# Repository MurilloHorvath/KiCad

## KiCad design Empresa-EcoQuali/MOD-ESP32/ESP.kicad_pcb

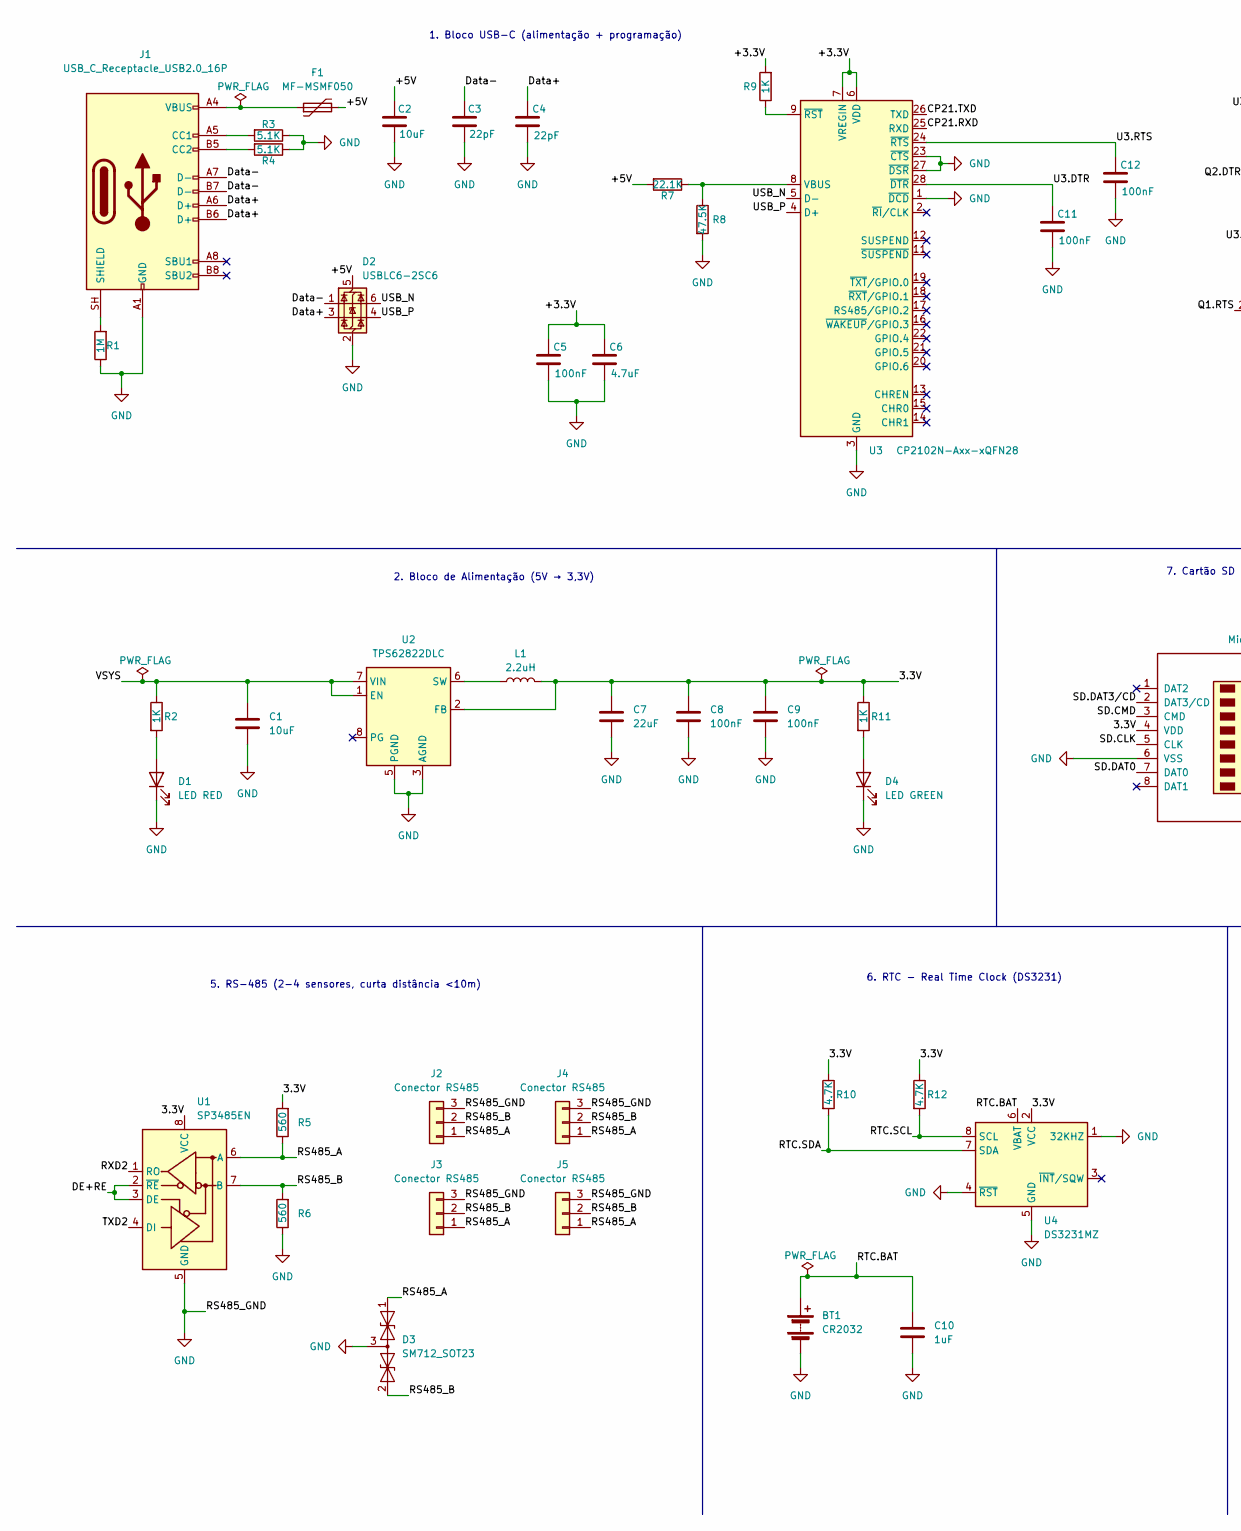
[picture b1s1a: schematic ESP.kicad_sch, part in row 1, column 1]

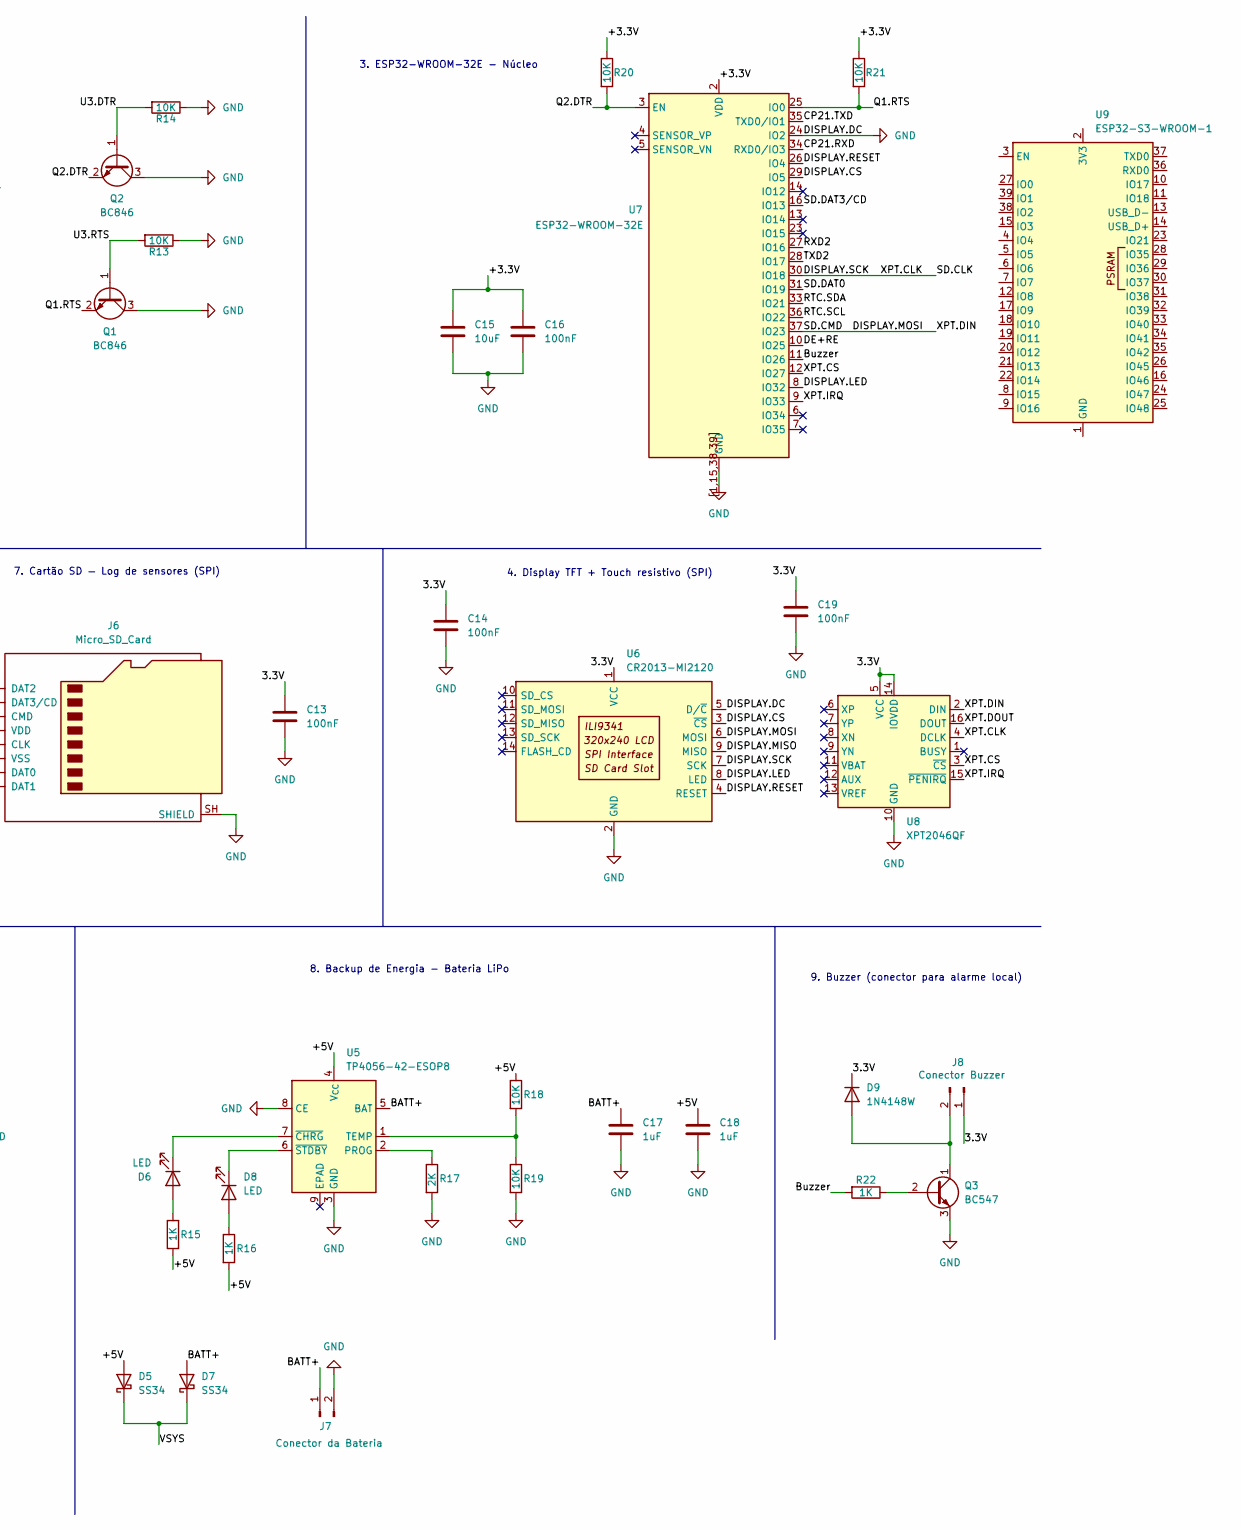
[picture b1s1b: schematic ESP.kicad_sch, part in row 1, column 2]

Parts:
BT1: CR2032; BatteryHolder_Keystone_103_1x20mm
C1, C2, C15: 10uF; C_0805_2012Metric
C3, C4: 22pF; C_0603_1608Metric
C5, C8, C9, C11, C12, C13, C14, C16, C19: 100nF; C_0603_1608Metric
C6: 4.7uF; C_0603_1608Metric
C7: 22uF; C_0805_2012Metric
C10, C17, C18: 1uF; C_0603_1608Metric
D1: LED RED; LED_0603_1608Metric
D2: USBLC6-2SC6; SOT-23-6
D3: SM712_SOT23; SOT-23
D4: LED GREEN; LED_0603_1608Metric
D5, D7: SS34; D_SMA
D6, D8: LED; LED_0603_1608Metric
D9: 1N4148W; D_DO-35_SOD27_P12.70mm_Horizontal
F1: MF-MSMF050; Fuse_1206_3216Metric
J1: USB_C_Receptacle_USB2.0_16P; USB_C_Receptacle_GCT_USB4105-xx-A_16P_TopMnt_Horizontal
J2, J3, J4, J5: Conector RS485; PinHeader_1x03_P2.54mm_Vertical
J6: Micro_SD_Card; microSD_HC_Molex_104031-0811
J7: Conector da Bateria; JST_XH_B2B-XH-A_1x02_P2.50mm_Vertical
J8: Conector Buzzer; JST_XH_B2B-XH-A_1x02_P2.50mm_Vertical
L1: 2.2uH; L_0805_2012Metric
Q1, Q2: BC846; SOT-23
Q3: BC547; TO-92_Inline
R1: 1M; R_0603_1608Metric
R2, R9, R11, R15, R16, R22: 1K; R_0603_1608Metric
R3, R4: 5.1K; R_0603_1608Metric
R5, R6: 560; R_0603_1608Metric
R7: 22.1K; R_0603_1608Metric
R8: 47.5K; R_0603_1608Metric
R10, R12: 4.7K; R_0603_1608Metric
R13, R14, R18, R19, R20, R21: 10K; R_0603_1608Metric
R17: 2K; R_0603_1608Metric
U1: SP3485EN; SOIC-8_3.9x4.9mm_P1.27mm
U2: TPS62822DLC; Texas_VSON-HR-8_1.5x2mm_P0.5mm
U3: CP2102N-Axx-xQFN28; QFN-28-1EP_5x5mm_P0.5mm_EP3.35x3.35mm_ThermalVias
U4: DS3231MZ; SOIC-16_3.9x9.9mm_P1.27mm
U5: TP4056-42-ESOP8; SOIC-8_3.9x4.9mm_P1.27mm
U6: CR2013-MI2120
U7: ESP32-WROOM-32E
U8: XPT2046QF; QFN-16-1EP_4x4mm_P0.65mm_EP2.1x2.1mm
U9: ESP32-S3-WROOM-1

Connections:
/3.3V: C7.1, C8.1, C9.1, C13.1, C14.1, C19.1, D9.1 (K), J6.4 (VDD), J8.1, L1.2, R5.2, R10.1, R11.1, R12.1, U1.8 (VCC), U2.2 (FB), U4.2 (VCC), U6.1 (VCC), U8.5 (VCC), U8.14 (IOVDD)
/+3.3V: C5.1, C6.1, C15.1, C16.1, R9.2, R20.1, R21.1, U3.6 (VDD), U3.7 (VREGIN), U7.2 (VDD)
/+5V: C2.1, C18.1, D2.5 (VBUS), D5.2 (A), F1.2, R7.2, R15.1, R16.2, R18.1, U5.4 (V_{CC})
/BATT+: C17.1, D7.2 (A), J7.1, U5.5 (BAT)
/Buzzer: R22.2, U7.11 (IO26)
/CP21.RXD: U3.25 (RXD), U7.34 (RXD0/IO3)
/CP21.TXD: U3.26 (TXD), U7.35 (TXD0/IO1)
/DE+RE: U1.2 (~RE), U1.3 (DE), U7.10 (IO25)
/DISPLAY.CS: U6.3 (~CS), U7.29 (IO5)
/DISPLAY.LED: U6.8 (LED), U7.8 (IO32)
/DISPLAY.MISO: U6.9 (MISO)
/DISPLAY.MOSI: J6.3 (CMD), U6.6 (MOSI), U7.37 (IO23), U8.2 (DIN)
/DISPLAY.RESET: U6.4 (RESET), U7.26 (IO4)
/DISPLAY.SCK: J6.5 (CLK), U6.7 (SCK), U7.30 (IO18), U8.4 (DCLK)
/Data+: C4.1, D2.3 (I/O2), J1.A6 (D+), J1.B6 (D+)
/Data-: C3.1, D2.1 (I/O1), J1.A7 (D-), J1.B7 (D-)
/Q1.RTS: Q1.2 (E), R21.2, U7.25 (IO0)
/Q2.DTR: Q2.2 (E), R20.2, U7.3 (EN)
/RS485_A: D3.1 (A1), J2.1, J3.1, J4.1, J5.1, R5.1, U1.6 (A)
/RS485_B: D3.2 (A2), J2.2, J3.2, J4.2, J5.2, R6.2, U1.7 (B)
/RTC.BAT: BT1.1 (+), C10.1, U4.6 (VBAT)
/RTC.SCL: R12.2, U4.8 (SCL), U7.36 (IO22)
/RTC.SDA: R10.2, U4.7 (SDA), U7.33 (IO21)
/RXD2: U1.1 (RO), U7.27 (IO16)
/SD.DAT0: J6.7 (DAT0), U7.31 (IO19)
/SD.DAT3/CD: J6.2 (DAT3/CD), U7.16 (IO13)
/TXD2: U1.4 (DI), U7.28 (IO17)
/U3.DTR: C11.1, Q2.1 (B), R14.2, U3.28 (~DTR)
/U3.RTS: C12.1, Q1.1 (B), R13.2, U3.24 (~RTS)
/USB_N: D2.6 (I/O1), U3.5 (D-)
/USB_P: D2.4 (I/O2), U3.4 (D+)
/VSYS: C1.1, D5.1 (K), D7.1 (K), R2.1, U2.1 (EN), U2.7 (VIN)
/XPT.CS: U7.12 (IO27), U8.3 (~CS)
/XPT.DOUT: U8.16 (DOUT)
/XPT.IRQ: U7.9 (IO33), U8.15 (~PENIRQ)
GND: BT1.2 (-), C1.2, C2.2, C3.2, C4.2, C5.2, C6.2, C7.2, C8.2, C9.2, C10.2, C11.2, C12.2, C13.2, C14.2, C15.2, C16.2, C17.2, C18.2, C19.2, D1.1 (K), D2.2 (GND), D3.3 (common), D4.1 (K), J1.A1 (GND), J1.A12 (GND), J1.B1 (GND), J1.B12 (GND), J2.3, J3.3, J4.3, J5.3, J6.6 (VSS), J6.SH (SHIELD), J7.2, Q1.3 (C), Q2.3 (C), Q3.3 (E), R1.1, R3.1, R4.1, R6.1, R8.2, R13.1, R14.1, R17.2, R19.2, U1.5 (GND), U2.3 (AGND), U2.5 (PGND), U3.1 (~DCD), U3.3 (GND), U3.23 (~CTS), U3.27 (~DSR), U3.29 (GND), U4.1 (32KHZ), U4.4 (~RST), U4.5 (GND), U5.3 (GND), U5.8 (CE), U6.2 (GND), U6.5 (D/~C), U7.1 (GND), U7.15 (GND), U7.24 (IO2), U7.38 (GND), U7.39 (GND), U7.[1,15,38,39] (GND), U8.10 (GND)
unnamed: D1.2 (A), R2.2
unnamed: D4.2 (A), R11.2
unnamed: D6.2 (A), R15.2
unnamed: D6.1 (K), U5.7 (~CHRG)
unnamed: D8.2 (A), R16.1
unnamed: D8.1 (K), U5.6 (~STDBY)
unnamed: D9.2 (A), J8.2, Q3.1 (C)
unnamed: F1.1, J1.A4 (VBUS), J1.A9 (VBUS), J1.B4 (VBUS), J1.B9 (VBUS)
unnamed: J1.A5 (CC1), R3.2
unnamed: J1.B5 (CC2), R4.2
unnamed: J1.SH (SHIELD), R1.2
unnamed: Q3.2 (B), R22.1
unnamed: L1.1, U2.6 (SW)
unnamed: R7.1, R8.1, U3.8 (VBUS)
unnamed: R9.1, U3.9 (~RST)
unnamed: R17.1, U5.2 (PROG)
unnamed: R18.2, R19.1, U5.1 (TEMP)
unnamed: U9.1 (GND), U9.40 (GND), U9.41 (GND)

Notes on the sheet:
9. Buzzer (conector para alarme local)
6. RTC - Real Time Clock (DS3231)
3. ESP32-WROOM-32E - Núcleo
5. RS-485 (2-4 sensores, curta distância <10m)
7. Cartão SD — Log de sensores (SPI)
4. Display TFT + Touch resistivo (SPI)
2. Bloco de Alimentação (5V → 3,3V)
8. Backup de Energia - Bateria LiPo
1. Bloco USB-C (alimentação + programação)

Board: 2 copper layers, 72 parts (71 on the bottom side), 51 nets, no tracks yet.

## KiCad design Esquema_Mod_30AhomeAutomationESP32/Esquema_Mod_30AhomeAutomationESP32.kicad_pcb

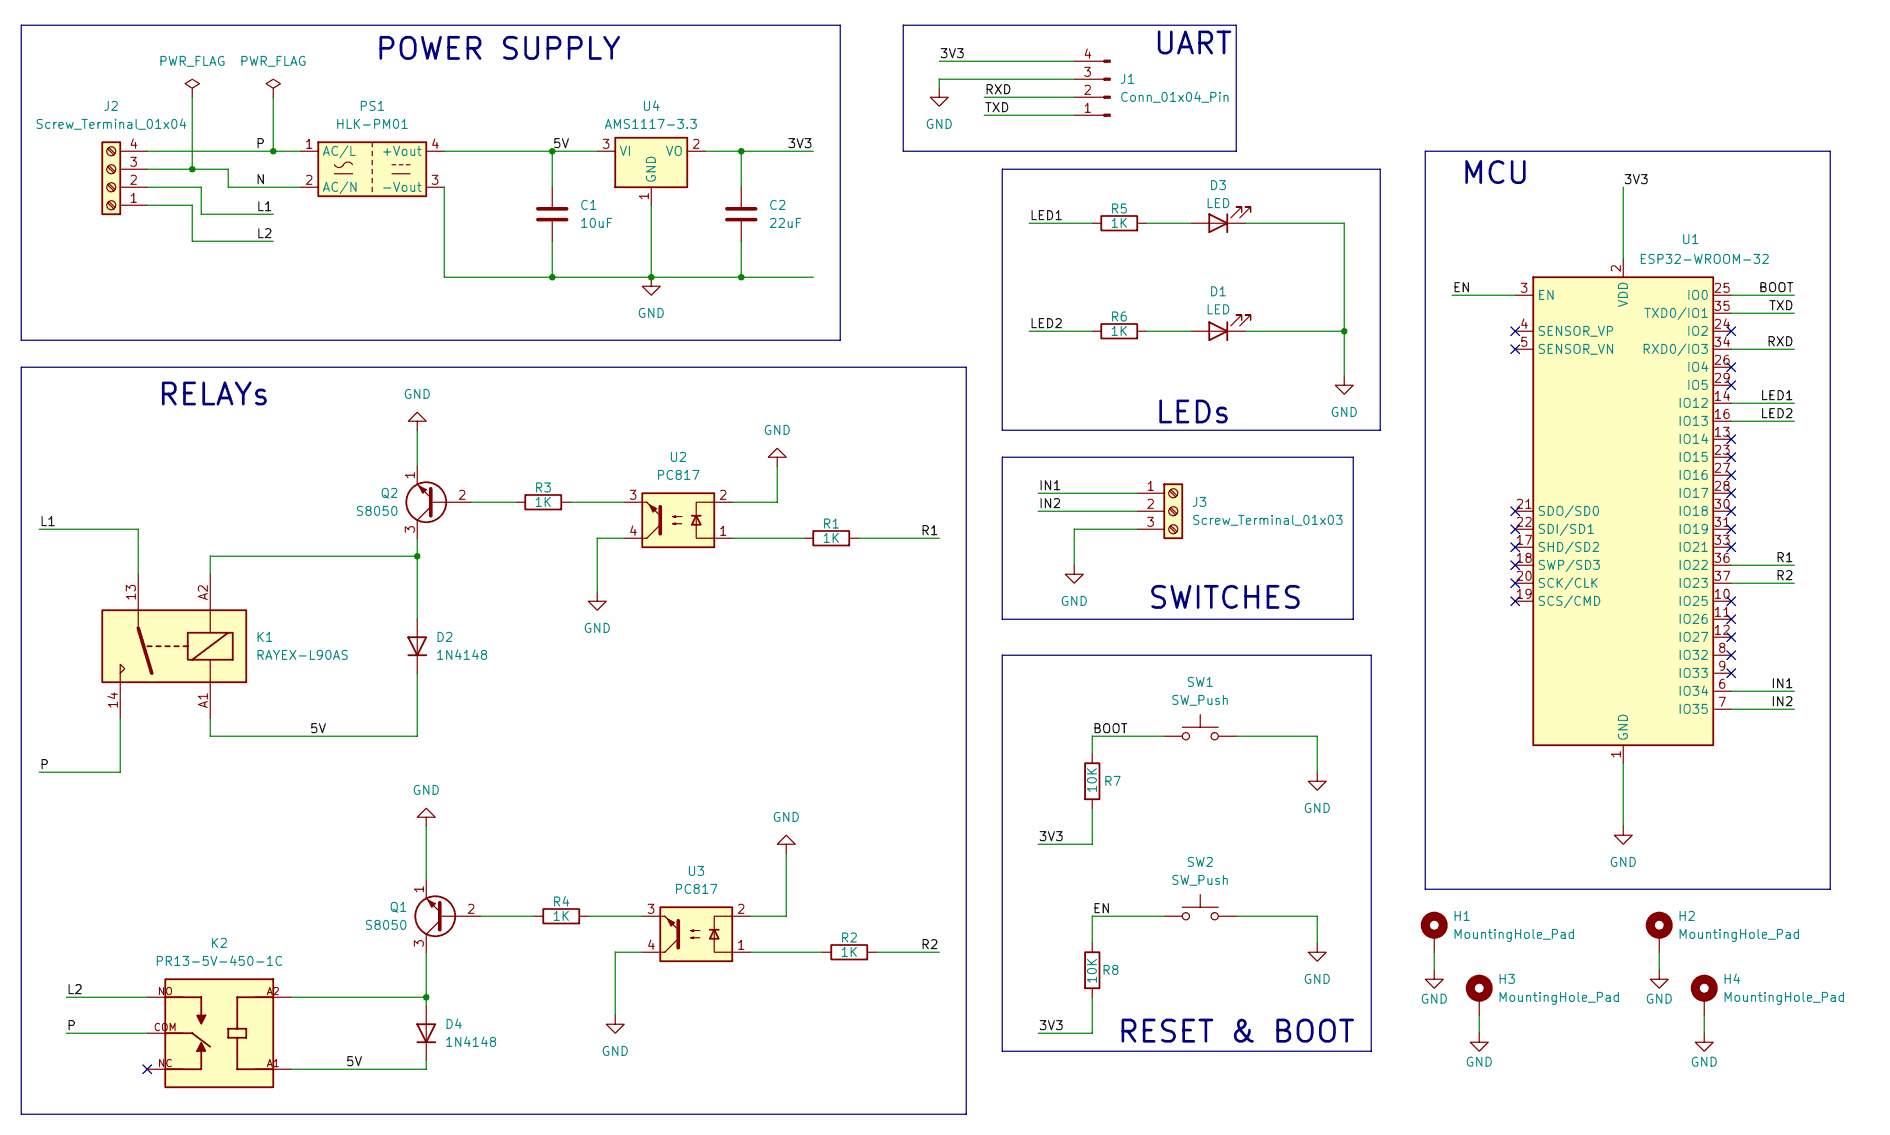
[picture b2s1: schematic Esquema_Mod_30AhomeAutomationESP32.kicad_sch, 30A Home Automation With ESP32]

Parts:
C1: 10uF; C_0805_2012Metric
C2: 22uF; C_0805_2012Metric
D1, D3: LED; LED_0805_2012Metric
D2, D4: 1N4148; D_DO-35_SOD27_P7.62mm_Horizontal
H1, H2, H3, H4: MountingHole_Pad; MountingHole_2.7mm_M2.5_Pad_Via
J1: Conn_01x04_Pin; PinHeader_1x04_P2.54mm_Vertical
J2: Screw_Terminal_01x04; TerminalBlock_MaiXu_MX126-5.0-04P_1x04_P5.00mm
J3: Screw_Terminal_01x03; TerminalBlock_MaiXu_MX126-5.0-03P_1x03_P5.00mm
K1: RAYEX-L90AS; Relay_SPST_RAYEX-L90AS
K2: PR13-5V-450-1C; RELAY_PR13-5V-450-1C; PARTREV 1.0
PS1: HLK-PM01; Converter_ACDC_Hi-Link_HLK-PMxx
Q1, Q2: S8050; TO-92_Inline
R1, R2, R3, R4, R5, R6: 1K; R_0805_2012Metric
R7, R8: 10K; R_0805_2012Metric
SW1, SW2: SW_Push; SW_PUSH_6mm
U1: ESP32-WROOM-32
U2, U3: PC817; DIP-4_W7.62mm
U4: AMS1117-3.3; SOT-223-3_TabPin2

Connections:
/3V3: C2.1, J1.4, R7.2, R8.2, U1.2 (VDD), U4.2 (VO)
/5V: C1.1, D2.1 (K), D4.1 (K), K1.A1, K2.A1, PS1.4 (+Vout), U4.3 (VI)
/BOOT: R7.1, SW1.1, U1.25 (IO0)
/EN: R8.1, SW2.1, U1.3 (EN)
/IN1: J3.1, U1.6 (IO34)
/IN2: J3.2, U1.7 (IO35)
/L1: J2.2, K1.13
/L2: J2.1, K2.NO
/LED1: R5.1, U1.14 (IO12)
/LED2: R6.1, U1.16 (IO13)
/N: J2.3, PS1.2 (AC/N)
/P: J2.4, K1.14, K2.COM, PS1.1 (AC/L)
/R1: R1.2, U1.36 (IO22)
/R2: R2.2, U1.37 (IO23)
/RXD: J1.2, U1.34 (RXD0/IO3)
/TXD: J1.1, U1.35 (TXD0/IO1)
GND: C1.2, C2.2, D1.1 (K), D3.1 (K), H1.1, H2.1, H3.1, H4.1, J1.3, J3.3, PS1.3 (-Vout), Q1.1 (E), Q2.1 (E), SW1.2, SW2.2, U1.1 (GND), U1.15 (GND), U1.38 (GND), U1.39 (GND), U2.2, U2.4, U3.2, U3.4, U4.1 (GND)
unnamed: D1.2 (A), R6.2
unnamed: D2.2 (A), K1.A2, Q2.3 (C)
unnamed: D3.2 (A), R5.2
unnamed: D4.2 (A), K2.A2, Q1.3 (C)
unnamed: Q1.2 (B), R4.1
unnamed: Q2.2 (B), R3.1
unnamed: R1.1, U2.1
unnamed: R2.1, U3.1
unnamed: R3.2, U2.3
unnamed: R4.2, U3.3

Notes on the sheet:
UART
LEDs
MCU
SWITCHES
RESET & BOOT
RELAYs
POWER SUPPLY

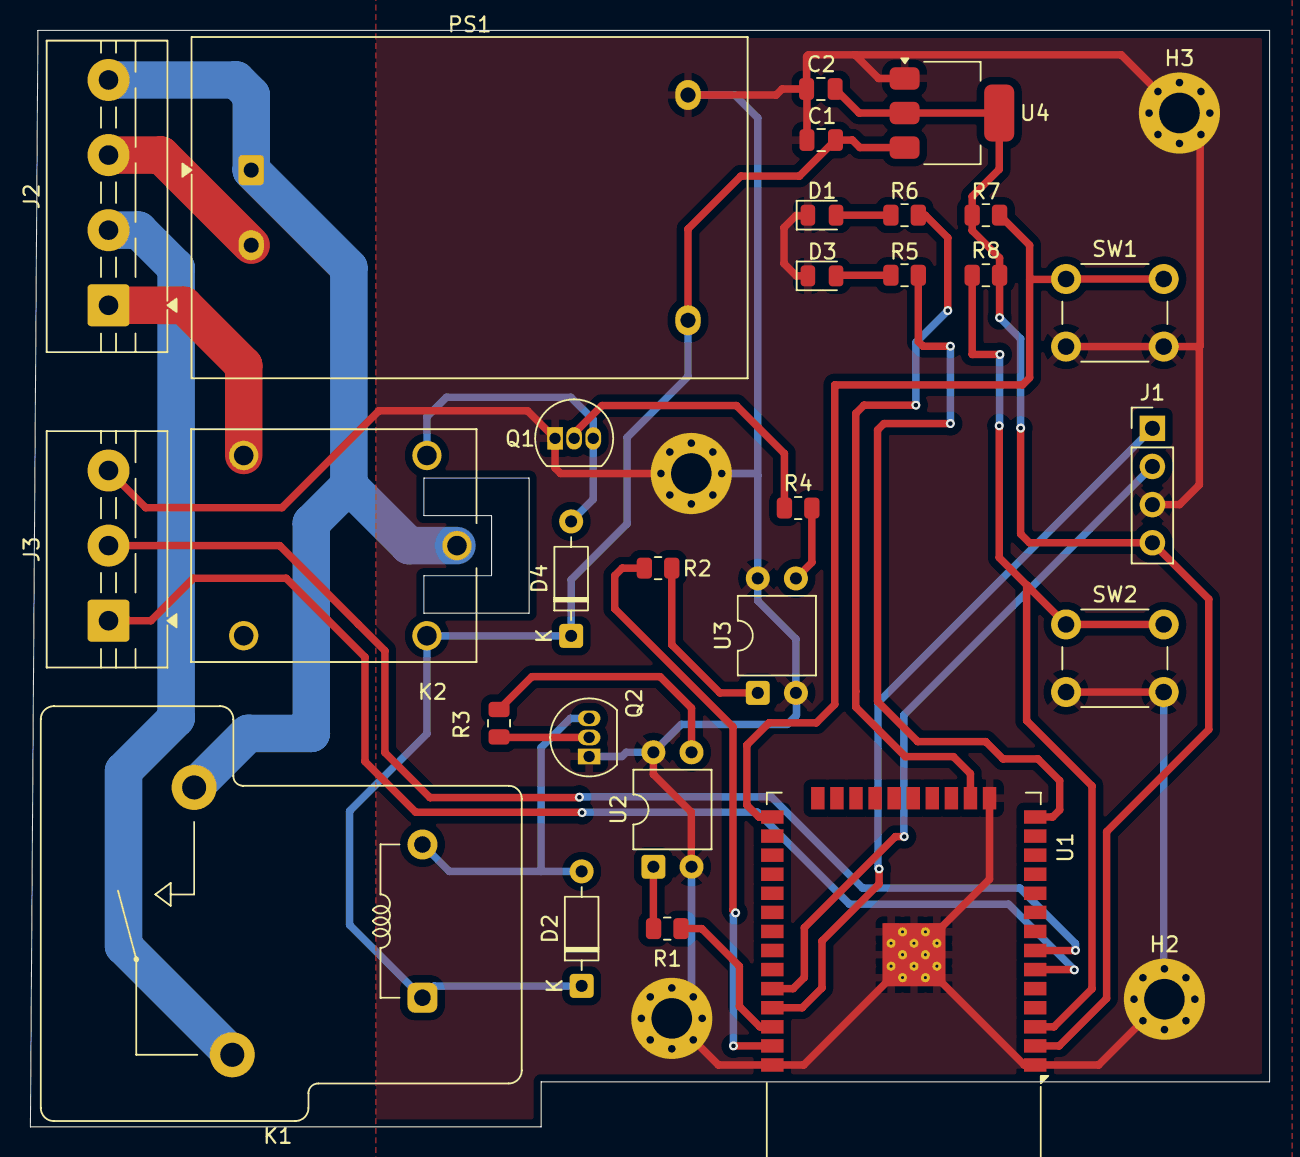
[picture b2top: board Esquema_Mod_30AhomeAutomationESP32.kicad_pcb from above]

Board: 2 copper layers, 82.5 x 73.0 mm, 32 parts (0 on the bottom side), 27 nets.

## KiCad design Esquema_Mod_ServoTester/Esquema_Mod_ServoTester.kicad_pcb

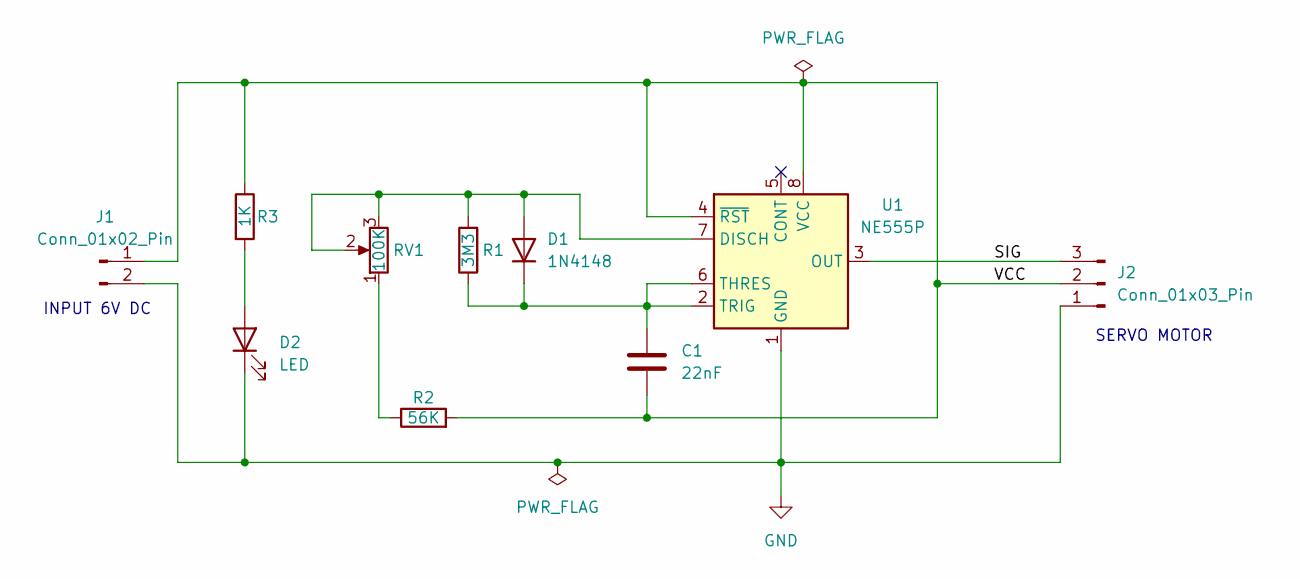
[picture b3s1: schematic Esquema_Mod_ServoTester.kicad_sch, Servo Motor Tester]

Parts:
C1: 22nF; C_Disc_D4.3mm_W1.9mm_P5.00mm
D1: 1N4148; D_DO-35_SOD27_P7.62mm_Horizontal
D2: LED; LED_D3.0mm
J1: Conn_01x02_Pin; PinHeader_1x02_P2.54mm_Horizontal
J2: Conn_01x03_Pin; PinHeader_1x03_P2.54mm_Horizontal
R1: 3M3; R_Axial_DIN0204_L3.6mm_D1.6mm_P7.62mm_Horizontal
R2: 56K; R_Axial_DIN0204_L3.6mm_D1.6mm_P7.62mm_Horizontal
R3: 1K; R_Axial_DIN0204_L3.6mm_D1.6mm_P7.62mm_Horizontal
RV1: 100K; Potentiometer_Alps_RK163_Single_Horizontal
U1: NE555P; DIP-8_W7.62mm

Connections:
/SIG: J2.3, U1.3 (OUT)
/VCC: C1.2, J1.1, J2.2, R2.2, R3.1, U1.4 (~RST), U1.8 (VCC)
GND: D2.1 (K), J1.2, J2.1, U1.1 (GND)
unnamed: D1.2 (A), R1.2, RV1.2, RV1.3, U1.7 (DISCH)
unnamed: C1.1, D1.1 (K), R1.1, U1.2 (TRIG), U1.6 (THRES)
unnamed: D2.2 (A), R3.2
unnamed: R2.1, RV1.1

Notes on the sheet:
INPUT 6V DC
SERVO MOTOR

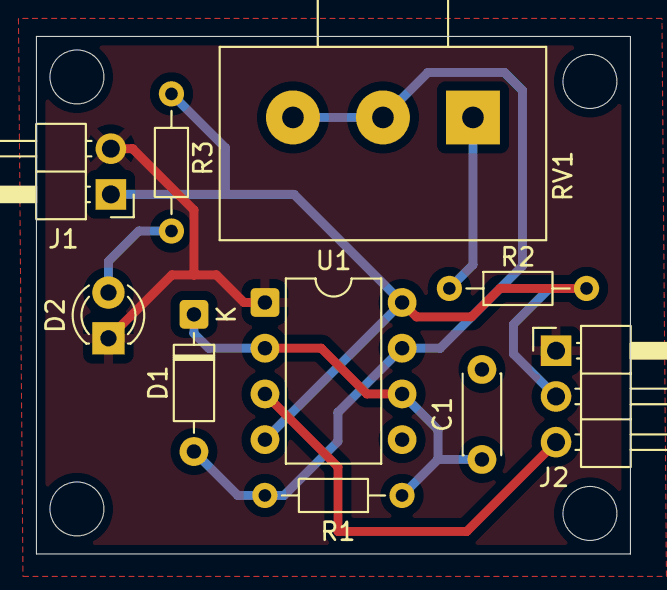
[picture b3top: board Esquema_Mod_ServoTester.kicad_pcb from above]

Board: 2 copper layers, 33.0 x 28.8 mm, 10 parts (0 on the bottom side), 7 nets.

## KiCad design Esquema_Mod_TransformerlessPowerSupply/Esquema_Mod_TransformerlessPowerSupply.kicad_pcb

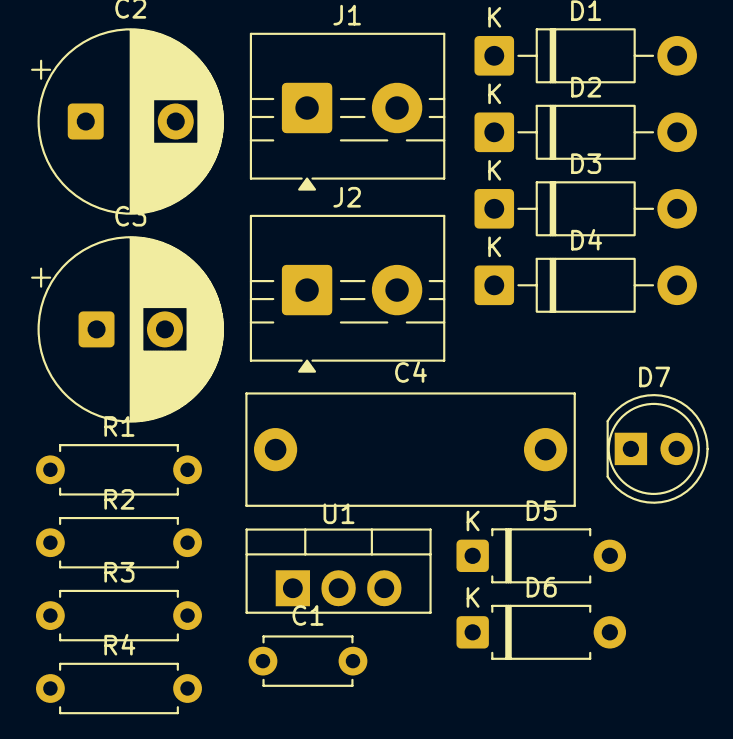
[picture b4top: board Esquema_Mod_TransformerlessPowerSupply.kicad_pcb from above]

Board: 2 copper layers, 18 parts (0 on the bottom side), 9 nets, no tracks yet.

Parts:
C1: 0.1uF; C_Disc_D4.7mm_W2.5mm_P5.00mm
C2: 1000uF; CP_Radial_D10.0mm_P5.00mm
C3: 470uF; CP_Radial_D10.0mm_P3.80mm
C4: 225k/2.2uF; C_Rect_L18.0mm_W6.0mm_P15.00mm_FKS3_FKP3
D1, D2, D3, D4: 1N4007; D_DO-41_SOD81_P10.16mm_Horizontal
D5, D6: D_Zener; D_A-405_P7.62mm_Horizontal
D7: LED; LED_D5.0mm
J1, J2: Screw_Terminal_01x02; TerminalBlock_MaiXu_MX126-5.0-02P_1x02_P5.00mm
R1, R2: 20k; R_Axial_DIN0207_L6.3mm_D2.5mm_P7.62mm_Horizontal
R3: 1M; R_Axial_DIN0207_L6.3mm_D2.5mm_P7.62mm_Horizontal
R4: 2.2k; R_Axial_DIN0207_L6.3mm_D2.5mm_P7.62mm_Horizontal
U1: LM7805_TO220; TO-220-3_Vertical

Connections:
/5V: C3.1, J2.1, U1.3 (VO)
GND: C1.2, C2.2, C3.2, D2.2 (A), D4.2 (A), D7.1 (K), J2.2, R1.2, R2.2, U1.2 (GND)
unnamed: C4.2, D1.2 (A), D2.1 (K), R3.2
unnamed: C1.1, C2.1, D1.1 (K), D3.1 (K), D5.1 (K), D6.1 (K), R4.1, U1.1 (VI)
unnamed: D3.2 (A), D4.1 (K), J1.1
unnamed: D5.2 (A), R1.1
unnamed: D6.2 (A), R2.1
unnamed: D7.2 (A), R4.2
unnamed: C4.1, J1.2, R3.1

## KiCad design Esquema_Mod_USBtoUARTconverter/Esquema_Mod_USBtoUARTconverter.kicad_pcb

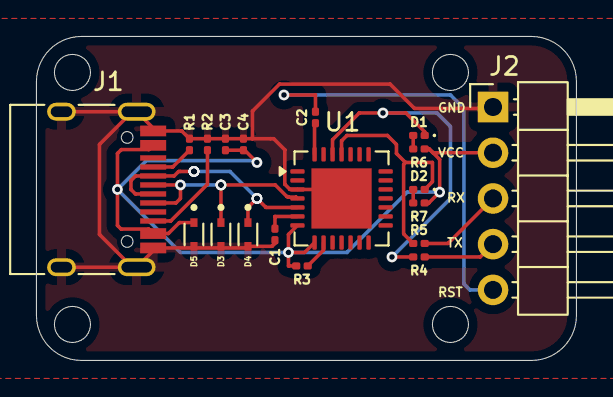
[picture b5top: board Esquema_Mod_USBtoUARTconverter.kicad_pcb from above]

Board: 2 copper layers, 30.0 x 18.0 mm, 19 parts (0 on the bottom side), 16 nets.

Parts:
C1, C2, C3, C4: 100nF; C_0201_0603Metric
D1, D2: LED; LED_0201_0603Metric
D3, D4, D5: LESD5D5.0CT1G; TVS_LESD5D5.0CT1G
J1: USB_C_Receptacle_USB2.0_16P; USB_C_Receptacle_HRO_TYPE-C-31-M-12
J2: Conn_01x05_Pin; PinHeader_1x05_P2.54mm_Horizontal
R1, R2: 5.1K; R_0201_0603Metric
R3: 10K; R_0201_0603Metric
R4, R5, R6, R7: 1K; R_0201_0603Metric
U1: CP2102N-Axx-xQFN28; QFN-28-1EP_5x5mm_P0.5mm_EP3.35x3.35mm

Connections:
/D+: D3.1, J1.A6 (D+), J1.B6 (D+), U1.4 (D+)
/D-: D4.1, J1.A7 (D-), J1.B7 (D-), U1.5 (D-)
/RST: C2.2, J2.5
/RX: J2.3, R5.1
/TX: J2.4, R4.1
/VBUS: C3.1, C4.1, D5.1, J1.A4 (VBUS), J1.A9 (VBUS), J1.B4 (VBUS), J1.B9 (VBUS), J2.2, R3.1, R6.1, R7.1, U1.7 (VREGIN), U1.8 (VBUS)
GND: C1.1, C3.2, C4.2, D3.2, D4.2, D5.2, J1.A1 (GND), J1.A12 (GND), J1.B1 (GND), J1.B12 (GND), J1.S1 (SHIELD), J2.1, R1.1, R2.1, U1.3 (GND), U1.29 (GND)
unnamed: D1.2 (A), R6.2
unnamed: D1.1 (K), R4.2, U1.26 (TXD)
unnamed: D2.2 (A), R7.2
unnamed: D2.1 (K), R5.2, U1.25 (RXD)
unnamed: J1.A5 (CC1), R1.2
unnamed: J1.B5 (CC2), R2.2
unnamed: C1.2, U1.6 (VDD)
unnamed: C2.1, U1.28 (~DTR)
unnamed: R3.2, U1.9 (~RST)

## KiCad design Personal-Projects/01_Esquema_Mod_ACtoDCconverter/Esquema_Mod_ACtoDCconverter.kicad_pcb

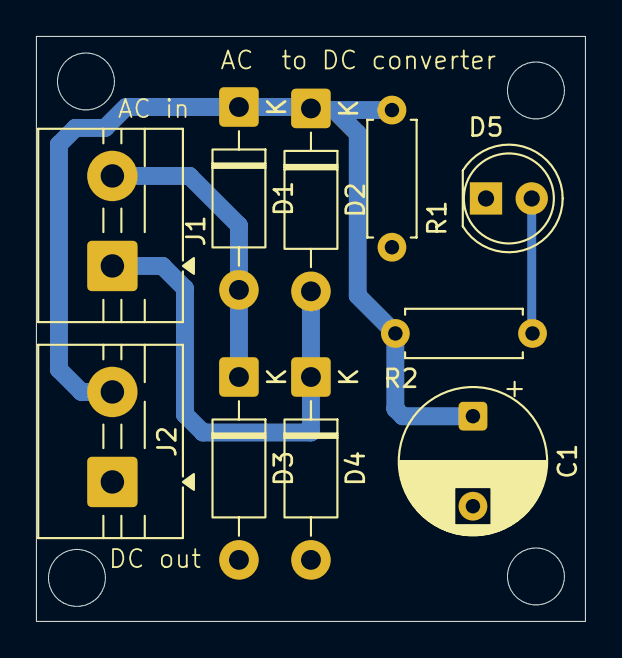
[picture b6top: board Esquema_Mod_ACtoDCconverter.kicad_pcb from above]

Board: 2 copper layers, 30.5 x 32.5 mm, 10 parts (0 on the bottom side), 5 nets.

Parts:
C1: 1000uF; CP_Radial_D8.0mm_P5.00mm
D1, D2, D3, D4: 1N4007; D_DO-41_SOD81_P10.16mm_Horizontal
D5: LED; LED_D5.0mm
J1, J2: Screw_Terminal_01x02; TerminalBlock_MaiXu_MX126-5.0-02P_1x02_P5.00mm
R1: 10K; R_Axial_DIN0207_L6.3mm_D2.5mm_P7.62mm_Horizontal
R2: 2.2K; R_Axial_DIN0207_L6.3mm_D2.5mm_P7.62mm_Horizontal

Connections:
/+V: C1.1, D1.1 (K), D2.1 (K), J2.2, R1.1, R2.1
GND: C1.2, D3.2 (A), D4.2 (A), D5.1 (K), J2.1, R1.2
unnamed: D1.2 (A), D3.1 (K), J1.2
unnamed: D2.2 (A), D4.1 (K), J1.1
unnamed: D5.2 (A), R2.2
